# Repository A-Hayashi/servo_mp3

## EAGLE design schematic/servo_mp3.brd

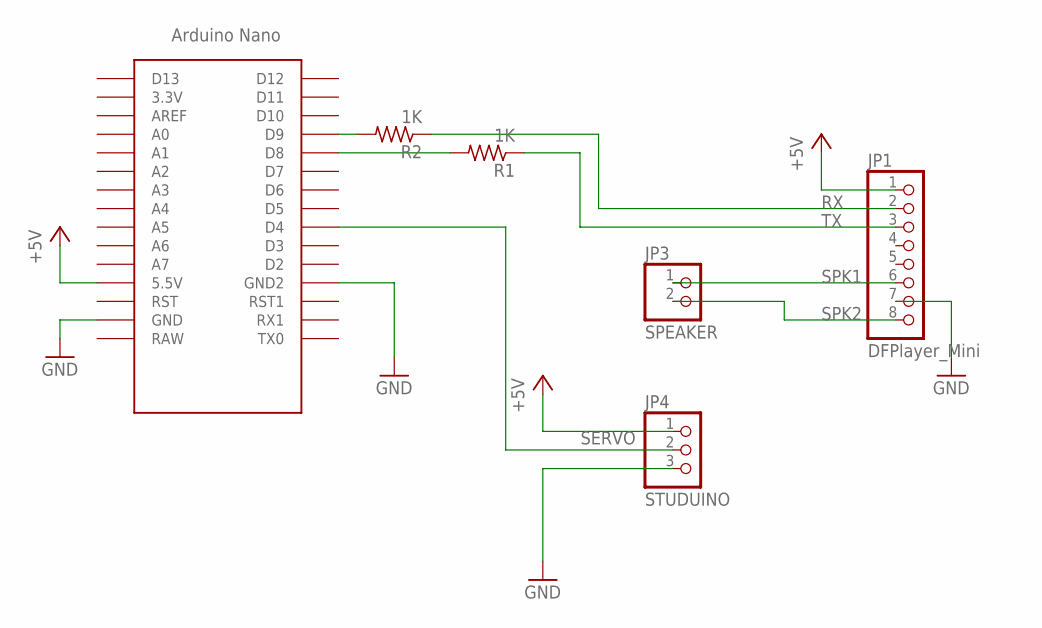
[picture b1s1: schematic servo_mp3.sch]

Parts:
JP1: DFPlayer_Mini; 1X08
JP3: SPEAKER; 1X02
JP4: STUDUINO; 1X03
R1, R2: 1K; 0207/12
U$1: NANO

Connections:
+5V: JP1.1, JP4.1, U$1.5V (5.5V)
GND: JP1.7, JP4.3, U$1.GND, U$1.GND1 (GND2)
unnamed: R2.2, U$1.D9
unnamed: R1.2, U$1.D8
RX: JP1.2, R2.1
SERVO: JP4.2, U$1.D4
SPK1: JP1.6, JP3.1
SPK2: JP1.8, JP3.2
TX: JP1.3, R1.1

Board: 2 copper layers, 6 parts (0 on the bottom side), 9 nets, no tracks yet.

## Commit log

2019-01-22 mp3再生単体動作確認済
2019-01-22 パルスに応じたmp3を再生する
2019-01-22 studuino
2019-01-22 回路図追加
